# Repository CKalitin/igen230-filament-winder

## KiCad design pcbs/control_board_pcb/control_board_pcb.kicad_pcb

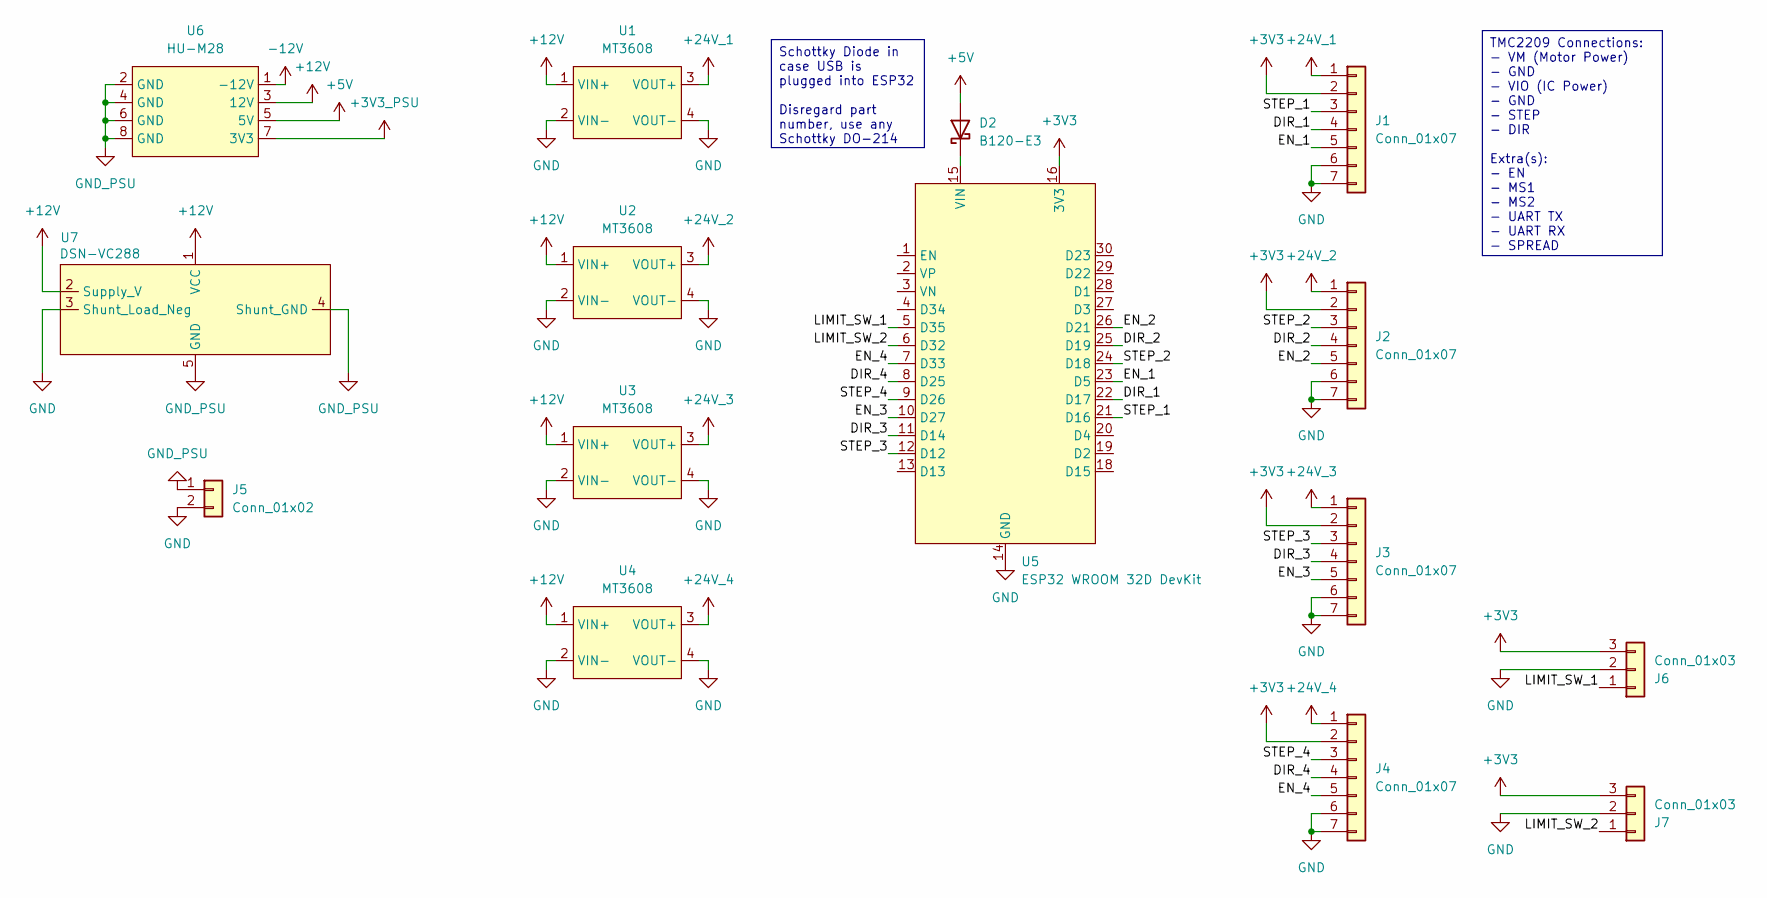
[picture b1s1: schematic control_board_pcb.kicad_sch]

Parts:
D2: B120-E3; D_SMA
J1, J2, J3, J4: Conn_01x07; JST_XH_B7B-XH-A_1x07_P2.50mm_Vertical
J5: Conn_01x02; PinHeader_1x02_P2.54mm_Vertical
J6, J7: Conn_01x03; JST_XH_B3B-XH-A_1x03_P2.50mm_Vertical
U1, U2, U3, U4: MT3608; MT3608_Boost_Converter
U5: ESP32 WROOM 32D DevKit; ESP32_Devkit_V1_DOIT_JWM_LessSilk
U6: HU-M28
U7: DSN-VC288; DSN-VC228_Pin-Holes

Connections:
+3V3: J1.2, J2.2, J3.2, J4.2, J6.3, J7.3, U5.16 (3V3)
+3V3_PSU: U6.7 (3V3)
+5V: D2.2 (A), U6.5 (5V)
+12V: U1.1 (VIN+), U2.1 (VIN+), U3.1 (VIN+), U4.1 (VIN+), U6.3 (12V), U7.1 (VCC), U7.2 (Supply_V)
+24V_1: J1.1, U1.3 (VOUT+)
+24V_2: J2.1, U2.3 (VOUT+)
+24V_3: J3.1, U3.3 (VOUT+)
+24V_4: J4.1, U4.3 (VOUT+)
-12V: U6.1 (-12V)
/DIR_1: J1.4, U5.22 (D17)
/DIR_2: J2.4, U5.25 (D19)
/DIR_3: J3.4, U5.11 (D14)
/DIR_4: J4.4, U5.8 (D25)
/EN_1: J1.5, U5.23 (D5)
/EN_2: J2.5, U5.26 (D21)
/EN_3: J3.5, U5.10 (D27)
/EN_4: J4.5, U5.7 (D33)
/LIMIT_SW_1: J6.1, U5.5 (D35)
/LIMIT_SW_2: J7.1, U5.6 (D32)
/STEP_1: J1.3, U5.21 (D16)
/STEP_2: J2.3, U5.24 (D18)
/STEP_3: J3.3, U5.12 (D12)
/STEP_4: J4.3, U5.9 (D26)
GND: J1.6, J1.7, J2.6, J2.7, J3.6, J3.7, J4.6, J4.7, J5.2, J6.2, J7.2, U1.2 (VIN-), U1.4 (VOUT-), U2.2 (VIN-), U2.4 (VOUT-), U3.2 (VIN-), U3.4 (VOUT-), U4.2 (VIN-), U4.4 (VOUT-), U5.14 (GND), U5.17 (GND), U7.3 (Shunt_Load_Neg)
GND_PSU: J5.1, U6.2 (GND), U6.4 (GND), U6.6 (GND), U6.8 (GND), U7.4 (Shunt_GND), U7.5 (GND)
unnamed: D2.1 (K), U5.15 (VIN)

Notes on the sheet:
Schottky Diode in case USB is plugged into ESP32 Disregard part number, use any Schottky DO-214
TMC2209 Connections: - VM (Motor Power) - GND - VIO (IC Power) - GND - STEP - DIR Extra(s): - EN - MS1 - MS2 - UART TX - UART RX - SPREAD

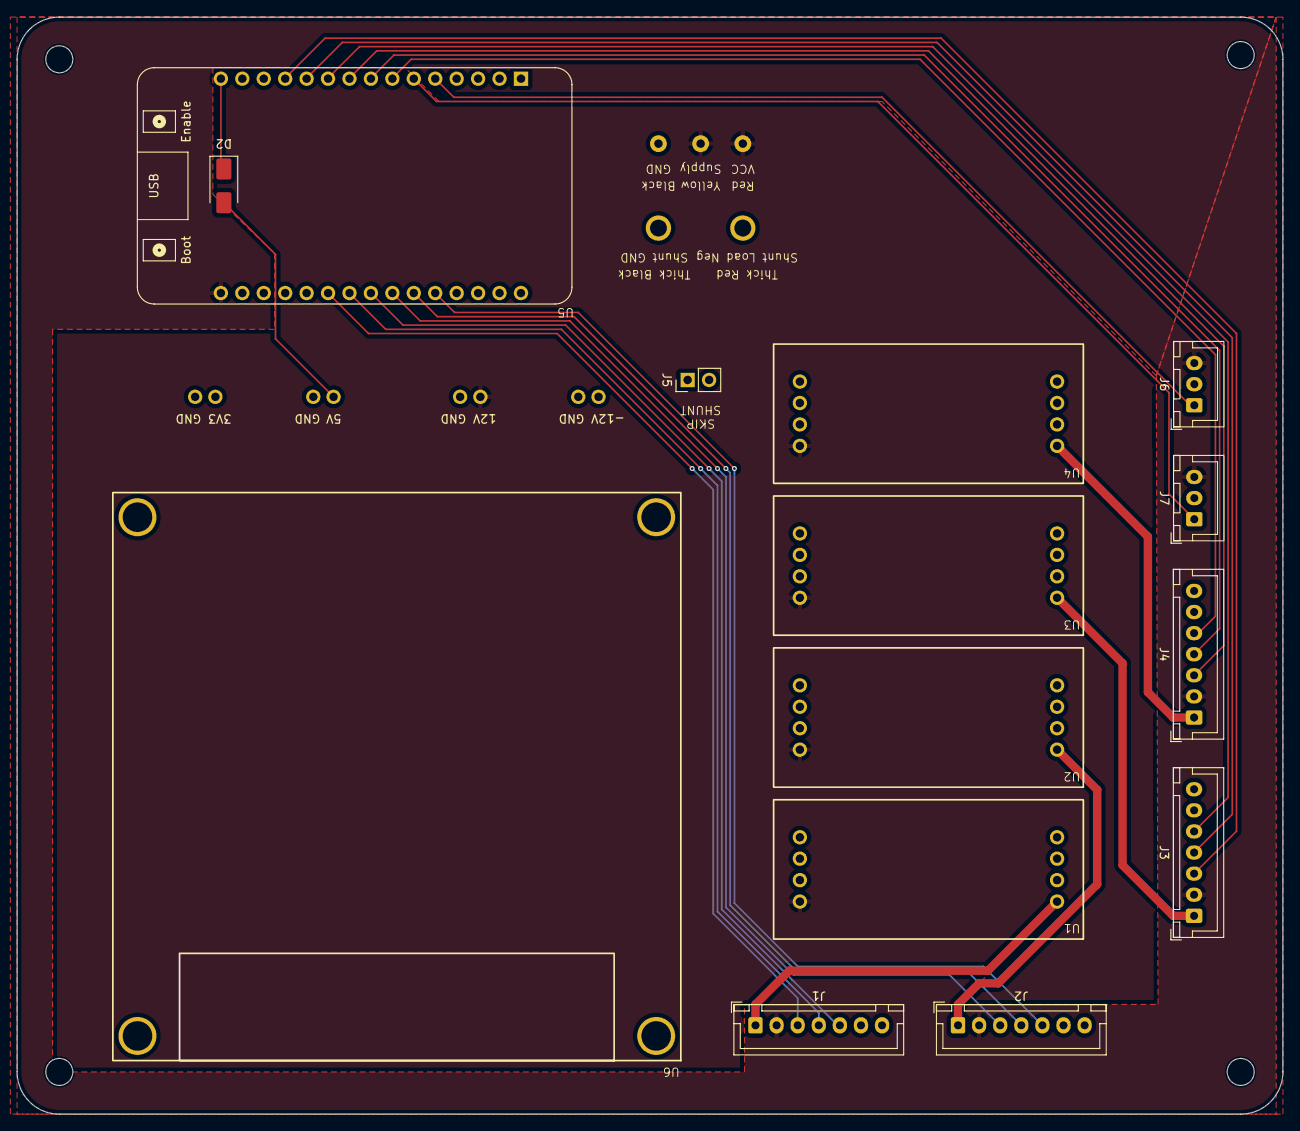
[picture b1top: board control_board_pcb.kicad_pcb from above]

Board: 4 copper layers, 150.0 x 130.0 mm, 15 parts (0 on the bottom side), 24 nets.

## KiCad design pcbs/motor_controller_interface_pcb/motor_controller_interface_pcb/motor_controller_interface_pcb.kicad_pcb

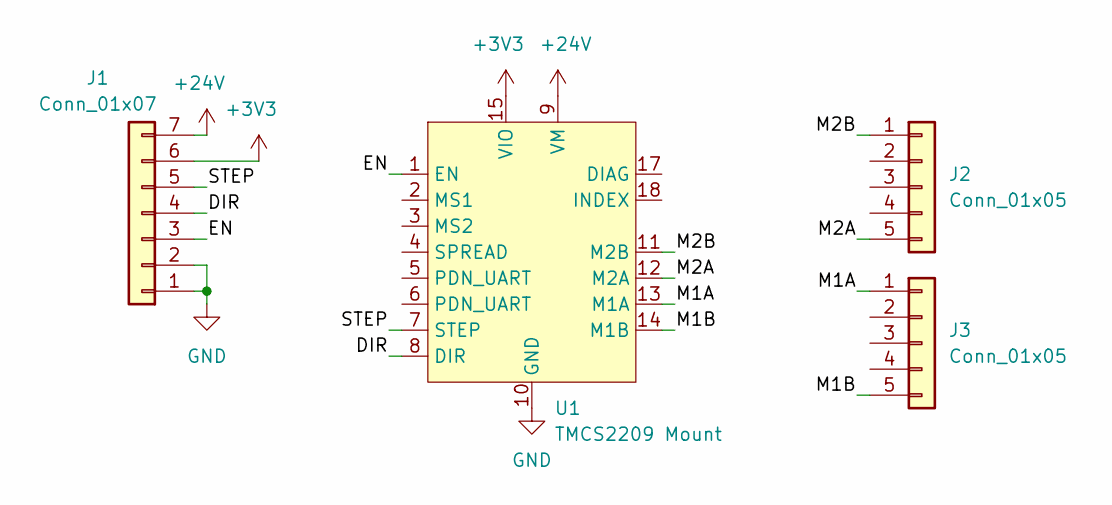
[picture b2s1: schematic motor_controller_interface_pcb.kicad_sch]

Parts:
J1: Conn_01x07; JST_XH_B7B-XH-A_1x07_P2.50mm_Vertical
J2, J3: Conn_01x05; JST_XH_B5B-XH-A_1x05_P2.50mm_Vertical
U1: TMCS2209 Mount; TMCS2209_Breakout_Board_Mount

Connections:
+3V3: J1.6, U1.15 (VIO)
+24V: J1.7, U1.9 (VM)
/DIR: J1.4, U1.8 (DIR)
/EN: J1.3, U1.1 (EN)
/M1A: J3.1, U1.13 (M1A)
/M1B: J3.5, U1.14 (M1B)
/M2A: J2.5, U1.12 (M2A)
/M2B: J2.1, U1.11 (M2B)
/STEP: J1.5, U1.7 (STEP)
GND: J1.1, J1.2, U1.10 (GND), U1.16 (GND)

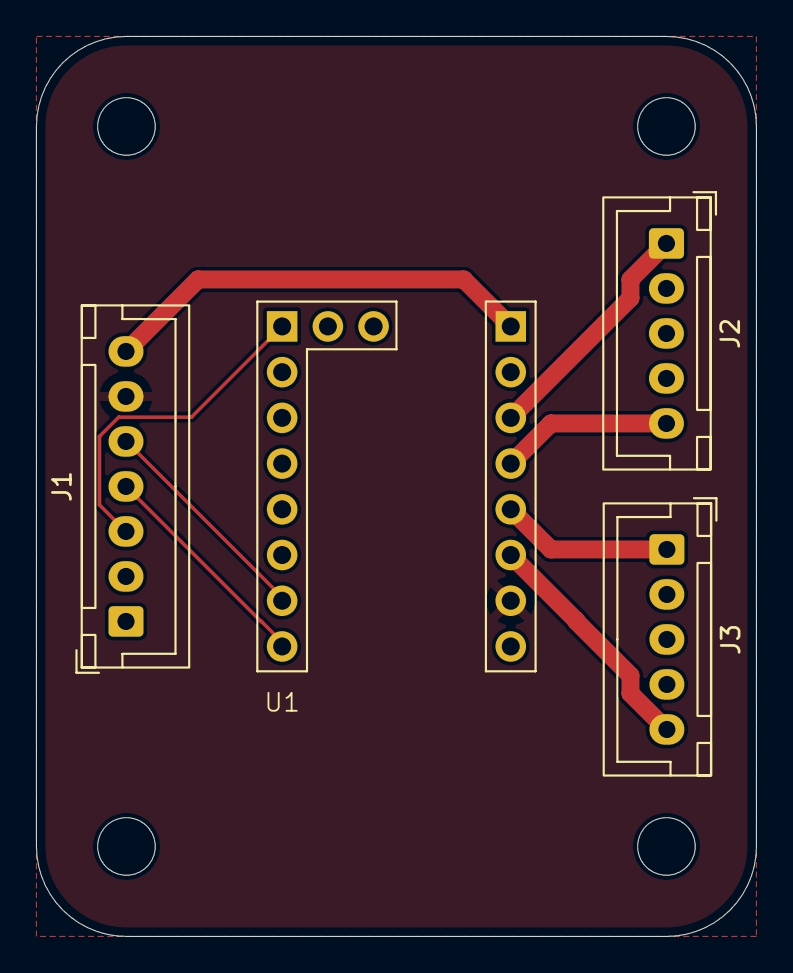
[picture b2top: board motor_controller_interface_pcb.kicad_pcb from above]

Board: 2 copper layers, 40.0 x 50.0 mm, 4 parts (0 on the bottom side), 10 nets.

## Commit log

2025-11-21 lewis structure of water
2025-11-21 Create Phys 157 tutorial 9.pdf
    test file
2026-01-15 add folder
2026-01-15 move
2026-01-15 delete DS Store
    Tim Apple why do you do this??
2026-01-21 Upload Loki Motor Script Init Firmware folder
2026-01-22 AccelStepper confirmed with 2 motors
2026-01-28 Simple limit switch implemenation
2026-02-10 pcb work
2026-02-25 Upload elias main.cpp
2026-02-26 Convert elias script into firmware structure
2026-02-27 better comments
2026-03-02 Control PCB nearly complete
2026-03-06 LED Blink
2026-03-06 Change DSN hole size
2026-03-07 Control Board PCB Ready
2026-03-07 Motor Controller Interface almost ready
2026-03-13 Elias 2 axis script (not tested)
2026-03-13 folder moved
2026-03-13 Firmware v2 structure
2026-03-13 Order PCBs
2026-03-13 Fixes
2026-03-13 enable
2026-03-13 enableenable
2026-03-13 baud rate
2026-03-13 baud rate again
2026-03-13 zeroing fix
2026-03-13 Update main.cpp
    changing so there is an infinte test loop
2026-03-14 bye bye serial
2026-03-17 better
2026-03-17 sync
2026-03-17 test
2026-03-18 4 axis pins
2026-03-18 3axis winding not tested
2026-03-18 separate axis files
2026-03-23 UI esp communication
2026-03-27 2 axis
2026-03-27 push
2026-03-27 3 axis
2026-03-27 testing
2026-03-28 3 axis done
2026-03-30 code
2026-04-01 Create 4axispinscorrectmason
2026-04-01 Rename 4axispinscorrectmason to 4axispinscorrectmason.cpp
2026-04-01 4axis
2026-04-02 zeroing fixed
2026-04-02 formatting
2026-04-02 more formating
2026-04-03 pasted 4 axis
2026-04-03 Create 4axisOwen
2026-04-03 4axisOwen
    V2
2026-04-04 Create Oh yeahh-most recent 4 axis script
    For elias bbg
2026-04-07 offset fixed
2026-04-08 4 axis update
2026-04-08 cleaned up 3 axis
2026-04-08 oush
